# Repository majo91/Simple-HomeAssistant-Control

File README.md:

# Simple-HomeAssistant-Control
Just a simple Smart Home Control Panel for Home Assistant. Based on ESPHome realized with a Wemos Mini

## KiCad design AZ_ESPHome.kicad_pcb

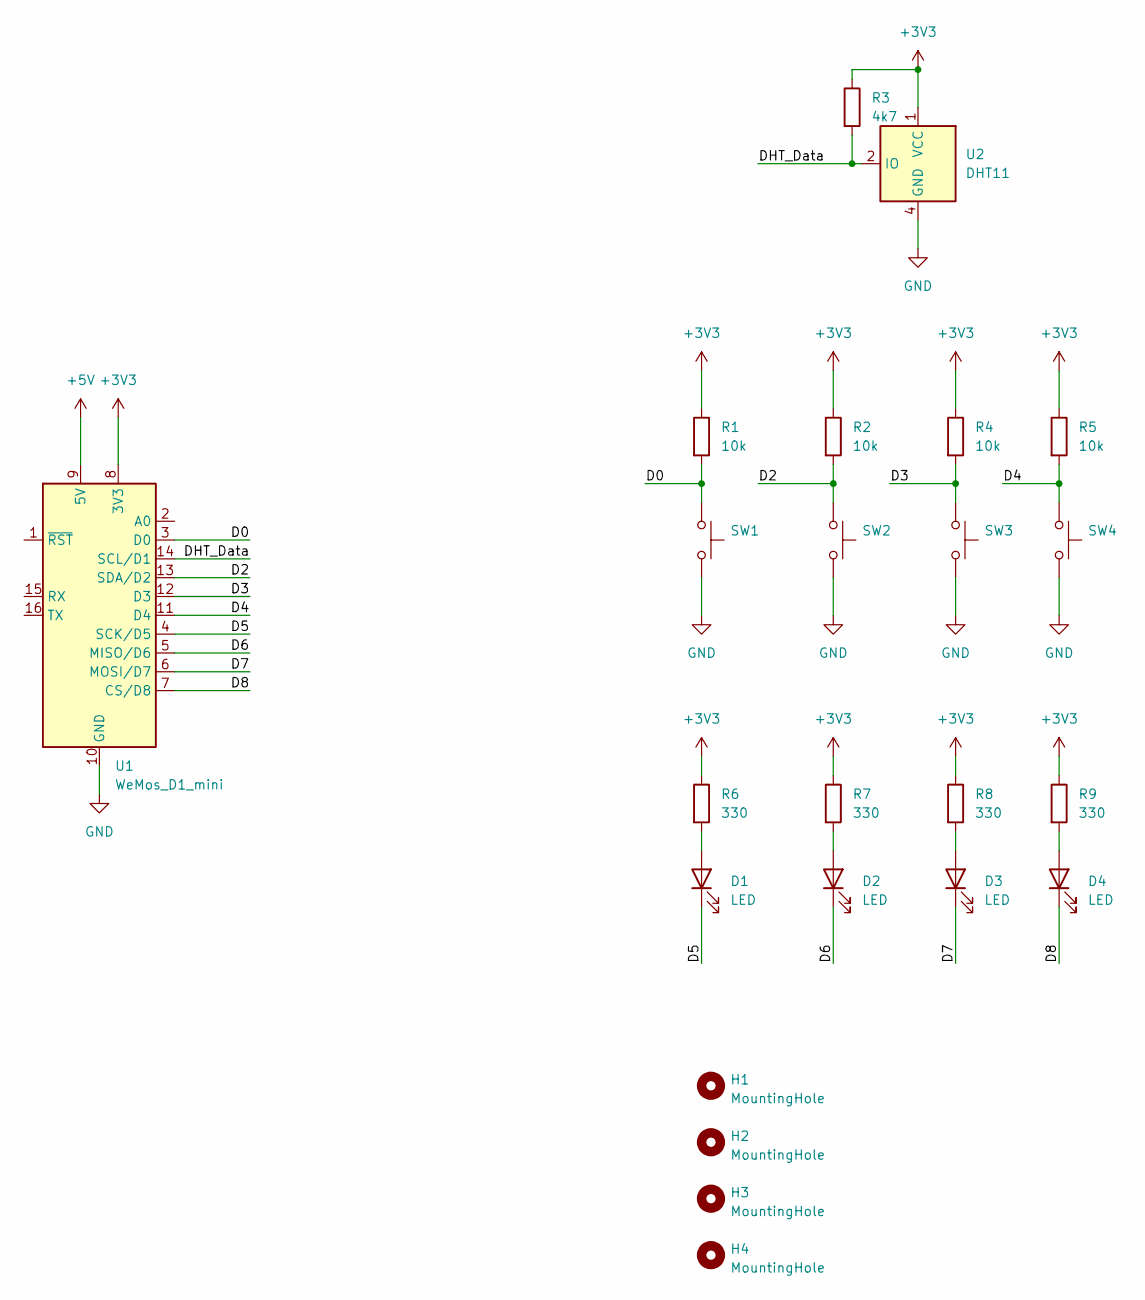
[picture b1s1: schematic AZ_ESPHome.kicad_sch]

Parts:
D1, D2, D3, D4: LED; LED_0603_1608Metric
H1, H2, H3, H4: MountingHole; MountingHole_3.2mm_M3
R1, R2, R4, R5: 10k; R_0603_1608Metric
R3: 4k7; R_0603_1608Metric
R6, R7, R8, R9: 330; R_0603_1608Metric
SW1, SW2, SW3, SW4: (no value)
U1: WeMos_D1_mini; WEMOS_D1_mini_light
U2: DHT11; Aosong_DHT11_5.5x12.0_P2.54mm

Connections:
+3V3: R1.1, R2.1, R3.1, R4.1, R5.1, R6.1, R7.1, R8.1, R9.1, U1.8 (3V3), U2.1 (VCC)
+5V: U1.9 (5V)
/D0: R1.2, SW1.1, U1.3 (D0)
/D2: R2.2, SW2.1, U1.13 (SDA/D2)
/D3: R4.2, SW3.1, U1.12 (D3)
/D4: R5.2, SW4.1, U1.11 (D4)
/D5: D1.1 (K), U1.4 (SCK/D5)
/D6: D2.1 (K), U1.5 (MISO/D6)
/D7: D3.1 (K), U1.6 (MOSI/D7)
/D8: D4.1 (K), U1.7 (CS/D8)
/DHT_Data: R3.2, U1.14 (SCL/D1), U2.2 (IO)
GND: SW1.2, SW2.2, SW3.2, SW4.2, U1.10 (GND), U2.4 (GND)
unnamed: D1.2 (A), R6.2
unnamed: D2.2 (A), R7.2
unnamed: D3.2 (A), R8.2
unnamed: D4.2 (A), R9.2

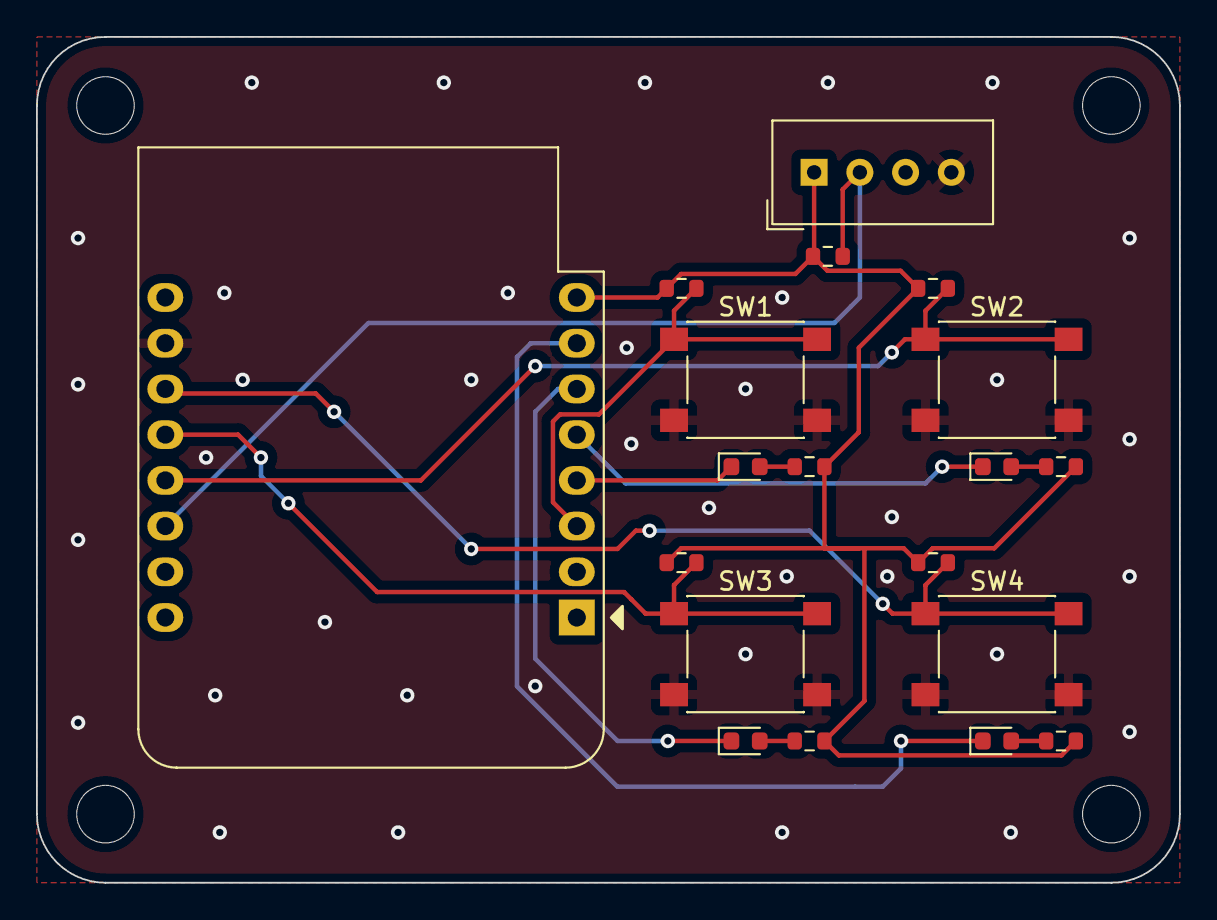
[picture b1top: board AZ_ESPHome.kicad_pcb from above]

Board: 2 copper layers, 63.5 x 47.0 mm, 23 parts (0 on the bottom side), 15 nets.

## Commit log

2022-04-06 added Readme
2022-04-06 added Sch as PDF
